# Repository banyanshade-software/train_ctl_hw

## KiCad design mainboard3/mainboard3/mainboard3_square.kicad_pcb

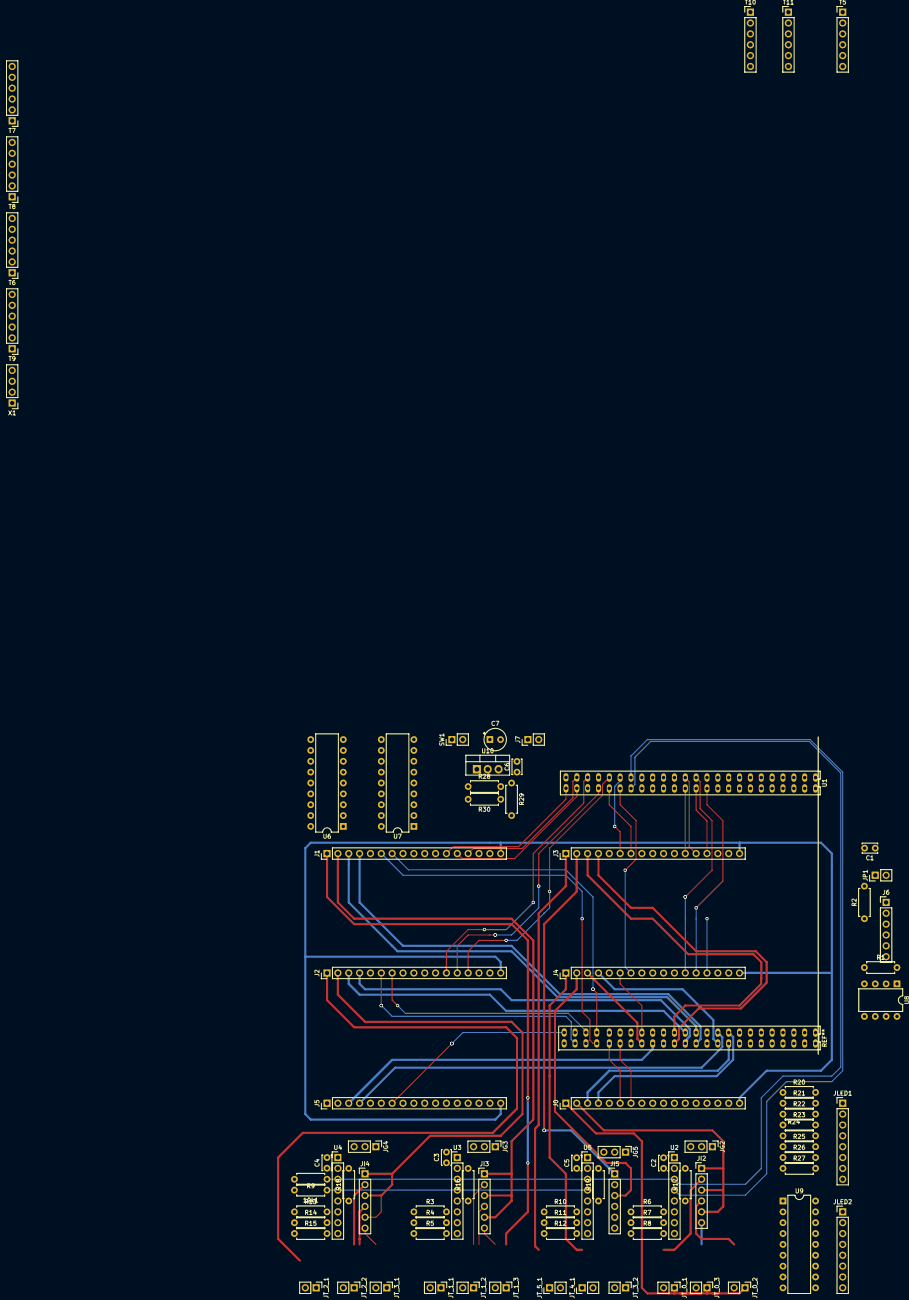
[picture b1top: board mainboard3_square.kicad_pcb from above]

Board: 2 copper layers, 88 parts (0 on the bottom side), 157 nets.

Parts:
10k1: R; R_Axial_DIN0207_L6.3mm_D2.5mm_P7.62mm_Horizontal
C1, C2, C3, C4, C5: 100nF; C_Disc_D3.4mm_W2.1mm_P2.50mm
C6: 0.1µF; C_Disc_D3.4mm_W2.1mm_P2.50mm
C7: 10µF; CP_Radial_Tantal_D5.0mm_P2.50mm
J0, J1, J2, J3, J4, J5: Conn_01x18; PinHeader_1x17_P2.54mm_Vertical
J6: Conn_01x06_Female; PinHeader_1x06_P2.54mm_Vertical
J7: Conn_01x02_Female; PinHeader_1x02_P2.54mm_Vertical
JG2, JG3, JG4, JG5: Conn_01x03_Female; PinHeader_1x03_P2.54mm_Vertical
JI2, JI3, JI4, JI5: Conn_01x06_Female; PinHeader_1x06_P2.54mm_Vertical
JLED1, JLED2: Conn_01x08_Female; PinHeader_1x08_P2.54mm_Vertical
JP1: Jumper; PinHeader_1x02_P2.54mm_Vertical
JT_0_1, JT_0_2, JT_0_3, JT_1_1, JT_1_2, JT_1_3, JT_2_1, JT_2_2, JT_3_1, JT_3_2, JT_4_1, JT_5_1: Screw_Terminal_01x02; PinHeader_1x02_P2.54mm_Vertical
R1, R20, R21, R22, R23, R24, R25, R26, R27: R; R_Axial_DIN0207_L6.3mm_D2.5mm_P7.62mm_Horizontal
R2: 120; R_Axial_DIN0207_L6.3mm_D2.5mm_P7.62mm_Horizontal
R3, R4, R5, R6, R7, R8, R9, R10, R11, R12, R13, R14, R15, R16, R17, R18, R19: 10k; R_Axial_DIN0207_L6.3mm_D2.5mm_P7.62mm_Horizontal
R28: 510; R_Axial_DIN0207_L6.3mm_D2.5mm_P7.62mm_Horizontal
R29: 200; R_Axial_DIN0207_L6.3mm_D2.5mm_P7.62mm_Horizontal
R30: 240; R_Axial_DIN0207_L6.3mm_D2.5mm_P7.62mm_Horizontal
SW1: SW_DIP_x01; PinHeader_1x02_P2.54mm_Vertical
T5, T6, T7, T8, T9, T10, T11: Screw_Terminal_01x06; PinHeader_1x06_P2.54mm_Vertical
U1: STM32_F4xx; STM32_F4XXrev
U2, U3, U4, U5: ModuleINA3221; PinHeader_1x08_P2.54mm_Vertical
U6, U7, U9: ULN2803A; DIP-18_W7.62mm
U8: MCP2551-I-P; DIP-8_W7.62mm
U10: LM317_TO220; TO-220-3_Vertical
X1: Screw_Terminal_01x04; PinHeader_1x04_P2.54mm_Vertical

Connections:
3V3: C2.2, C3.2, C4.2, C5.2, R3.1, R4.1, R5.1, R6.1, R7.1, R8.1, R10.1, R11.1, R12.1, R13.1, R14.1, R15.1, T10.2, U1.1, U1.2, U1.3, U1.4, U1.53, U1.54, U1.55, U1.56, U2.1, U3.1, U4.1, U5.1
5V: R20.1, R21.1, R22.1, R23.1, R24.1, R25.1, R26.1, R27.1, U1.49, U1.50, U1.51, U1.52, U9.10, X1.3
12Vunreg: C6.1, J0.17, J1.17, J2.17, J3.17, J4.17, J5.17, J7.2, T6.2, T6.5, T7.2, T7.5, T8.2, T8.5, T9.2, T9.5, U6.10, U7.10, U10.3, X1.1
+5V: C1.2, J6.3, U8.3
CAN_RX: U1.13, U8.4
CAN_TX: U1.14, U8.1
CT0_1: J0.12, U1.61
CT0_2: J0.13, U1.59
CT0_3: J0.14, U1.60
CT1_1: J1.12, U1.48
CT1_2: J1.13, U1.46
CT1_3: J1.14, U1.45
CT2_1: J2.12, U1.43
CT2_2: J2.13, U1.42
CT2_3: J2.14, U1.39
CT3_1: J3.12, U1.26
CT3_2: J3.13, U1.25
CT3_3: J3.14, U1.24
CT4_1: J4.12, U1.23
CT4_2: J4.13, U1.22
CT4_3: J4.14, U1.21
CT5_1: J5.12, U1.83
CT5_2: J5.13, U1.85
CT5_3: J5.14, U1.87
ETR1: T5.5, U1.84
GND: 10k1.2, C1.1, C2.1, C3.1, C4.1, C5.1, C6.2, C7.2, J0.16, J1.16, J2.16, J3.16, J4.16, J5.16, J6.2, J7.1, JG2.1, JG2.2, JG3.1, JG3.2, JG4.1, JG4.2, JG5.1, JG5.2, R1.1, R9.2, R29.2, T5.1, T10.1, U1.7, U1.8, U1.9, U1.10, U1.57, U1.58, U2.2, U3.2, U4.2, U5.2, U6.9, U7.9, U8.2, U9.9, X1.2
I1A: J0.2, JI2.1, JI2.3, JI2.5
I1B: JI2.2, JT_0_1.2
I2B: JI2.4, JT_0_2.2
I2C1_SCL: T5.4, T10.4, U1.15
I2C1_SDA: T5.3, T10.3, U1.16
I2C3_SCL: R9.1, U1.36, U2.3, U3.3, U4.3, U5.3
I2C3_SDA: 10k1.1, U1.35, U2.4, U3.4, U4.4, U5.4
I3B: JI2.6, JT_0_3.2
I4A: J1.2, JI3.1, JI3.3, JI3.5
I4B: JI3.2, JT_1_1.2
I5B: JI3.4, JT_1_2.2
I6B: JI3.6, JT_1_3.2
I7A: J2.2, JI4.1, JI4.3, JI4.5
I7B: JI4.2, JT_2_1.2
I8B: JI4.4, JT_2_2.2
I9B: JI4.6, JT_3_1.2
I10A: J3.2, JI5.1
I10B: JI5.2, JT_3_2.2
I11A: J4.2, JI5.3
I11B: JI5.4, JT_4_1.2
I12A: J5.2, JI5.5
I12B: JI5.6, JT_5_1.2
unnamed: C7.1, R30.1, SW1.1, U10.2
unnamed: J6.5, R2.1, U8.7
unnamed: J6.6, JP1.1, U8.6
unnamed: JG2.3, R17.2
unnamed: JG3.3, R16.2
unnamed: JG4.3, R18.2
unnamed: JG5.3, R19.2
unnamed: JLED1.1, R20.2
unnamed: JLED1.2, U9.18
unnamed: JLED1.3, R21.2
unnamed: JLED1.4, U9.17
unnamed: JLED1.5, R22.2
unnamed: JLED1.6, U9.16
unnamed: JLED1.7, R23.2
unnamed: JLED1.8, U9.15
unnamed: JLED2.1, R24.2
unnamed: JLED2.2, U9.14
unnamed: JLED2.3, R25.2
unnamed: JLED2.4, U9.13
unnamed: JLED2.5, R26.2
unnamed: JLED2.6, U9.12
unnamed: JLED2.7, R27.2
unnamed: JLED2.8, U9.11
unnamed: JP1.2, R2.2
unnamed: R1.2, U8.8
unnamed: R3.2, U3.6
unnamed: R4.2, U3.7
unnamed: R5.2, U3.8
unnamed: R6.2, U2.6
unnamed: R7.2, U2.7
unnamed: R8.2, U2.8
unnamed: R10.2, U5.6
unnamed: R11.2, U5.7
unnamed: R12.2, U5.8
unnamed: R13.2, U4.6
unnamed: R14.2, U4.7
unnamed: R15.2, U4.8
unnamed: R16.1, U3.5
unnamed: R17.1, U2.5
unnamed: R18.1, U4.5
unnamed: R19.1, U5.5
unnamed: R28.1, R30.2, U10.1
unnamed: R28.2, R29.1
unnamed: T6.1, U6.18
unnamed: T6.3, U6.17
unnamed: T6.4, U6.16
unnamed: T6.6, U6.15
unnamed: T7.1, U6.14
unnamed: T7.3, U6.13
unnamed: T7.4, U6.12
unnamed: T7.6, U6.11
unnamed: T8.1, U7.18
unnamed: T8.3, U7.17
unnamed: T8.4, U7.16
unnamed: T8.6, U7.15
unnamed: T9.1, U7.14
unnamed: T9.3, U7.13
unnamed: T9.4, U7.12
unnamed: T9.6, U7.11
PWM0_1: J0.6, U1.88
PWM0_2: J0.7, U1.86
PWM1_1: J1.6, U1.90
PWM1_2: J1.7, U1.89
PWM2_1: J2.6, U1.94
PWM2_2: J2.7, U1.91
PWM3_1: J3.6, U1.37
PWM3_2: J3.7, U1.40
PWM4_1: J4.6, U1.81
PWM4_2: J4.7, U1.38
PWM5_1: J5.6, U1.47
PWM5_2: J5.7, U1.95
R1: T11.2, U1.33
R2: T11.3, U1.34
R5: T11.6, U1.29
ROT1: T10.6, U1.44
ROT2: T10.5, U1.41
TRACK0_0: J0.1, JT_0_1.1, JT_0_2.1, JT_0_3.1
TRACK1_0: J1.1, JT_1_1.1, JT_1_2.1, JT_1_3.1
TRACK2_0: J2.1, JT_2_1.1, JT_2_2.1, JT_3_1.1
TRACK3_0: J3.1, JT_3_2.1
TRACK4_0: J4.1, JT_4_1.1
TRACK5_0: J5.1, JT_5_1.1
TURN1A: U1.93, U6.1
TURN2A: U1.96, U6.3
TURN2B: U1.18, U6.4
TURN3A: U1.19, U6.5
TURN3B: U1.20, U6.6
TURN4A: U1.62, U6.7
TURN4B: U1.64, U6.8
TURN5A: U1.63, U7.1
TURN5B: U1.28, U7.2
TURN6A: U1.79, U7.3
TURN6B: U1.92, U7.4
TURN7A: U1.27, U7.5
TURN7B: U1.30, U7.6
TURN8A: U1.11, U7.7
TURN8B: U1.12, U7.8
VSENSE0_0: J0.3, U1.66
VSENSE0_1: J0.4, U1.65
VSENSE1_0: J1.3, U1.71
VSENSE1_1: J1.4, U1.72
VSENSE2_0: J2.3, U1.73
VSENSE2_1: J2.4, U1.74
VSENSE3_0: J3.3, U1.75
VSENSE3_1: J3.4, U1.76
VSENSE4_0: J4.3, U1.82
VSENSE4_1: J4.4, U1.68
VSENSE5_0: J5.3, U1.80
VSENSE5_1: J5.4, U1.67

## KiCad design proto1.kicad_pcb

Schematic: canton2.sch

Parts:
C1: 0.1µF; C_Disc_D3.4mm_W2.1mm_P2.50mm
C2: 10µF; CP_Radial_Tantal_D5.0mm_P2.50mm
J1: Conn_01x18; PinHeader_1x16_P2.54mm_Horizontal
Q1, Q2, Q3, Q4: PN2222A; TO-92_Inline
R1: 240; R_Axial_DIN0207_L6.3mm_D2.5mm_P10.16mm_Horizontal
R2, R3, R4, R5, R6: R; R_Axial_DIN0207_L6.3mm_D2.5mm_P7.62mm_Horizontal
R7, R8, R9, R10, R15: 2200; R_Axial_DIN0207_L6.3mm_D2.5mm_P7.62mm_Horizontal
R12, R13: 10k; R_Axial_DIN0207_L6.3mm_D2.5mm_P7.62mm_Horizontal
R14: 2200; R_Axial_DIN0207_L6.3mm_D2.5mm_P10.16mm_Horizontal
R16: 3k; R_Axial_DIN0207_L6.3mm_D2.5mm_P7.62mm_Horizontal
U1: LM317_TO220; TO-220-3_Vertical
U2: CJMCU-4080; module_1x8
U3: ModuleDRV8833; module_2x6

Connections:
3.3V: J1.7, U2.4
12Vunreg: C1.1, U1.3 (VI)
CT0: J1.11, R7.2
CT1: J1.12, R8.2
CT2: J1.13, R9.2
CT3: J1.14, R10.2
GND: C1.2, C2.2, J1.16, Q1.1, Q2.1, Q3.1, Q4.1, R2.2, R14.2, R15.2, U2.1, U2.5, U3.10
ISENSE: J1.6, U2.8
unnamed: C2.1, R1.1, U1.2 (VO), U2.3
unnamed: Q1.2, R7.1
unnamed: Q1.3, R3.2
unnamed: Q2.2, R8.1
unnamed: Q2.3, R4.2
unnamed: Q3.2, R9.1
unnamed: Q3.3, R5.2
unnamed: Q4.2, R10.1
unnamed: Q4.3, R6.2
unnamed: R1.2, R2.1, R3.1, R4.1, R5.1, R6.1, U1.1 (ADJ)
unnamed: U2.2, U3.9
PWM1: J1.8, U3.7
PWM2: J1.9, U3.8
TRACK0: J1.1, R13.1, R16.1, U3.2
TRACK1: J1.2, R12.1, R16.2, U3.3
VSENSE0: J1.5, R12.2, R14.1
VSENSE1: J1.4, R13.2, R15.1

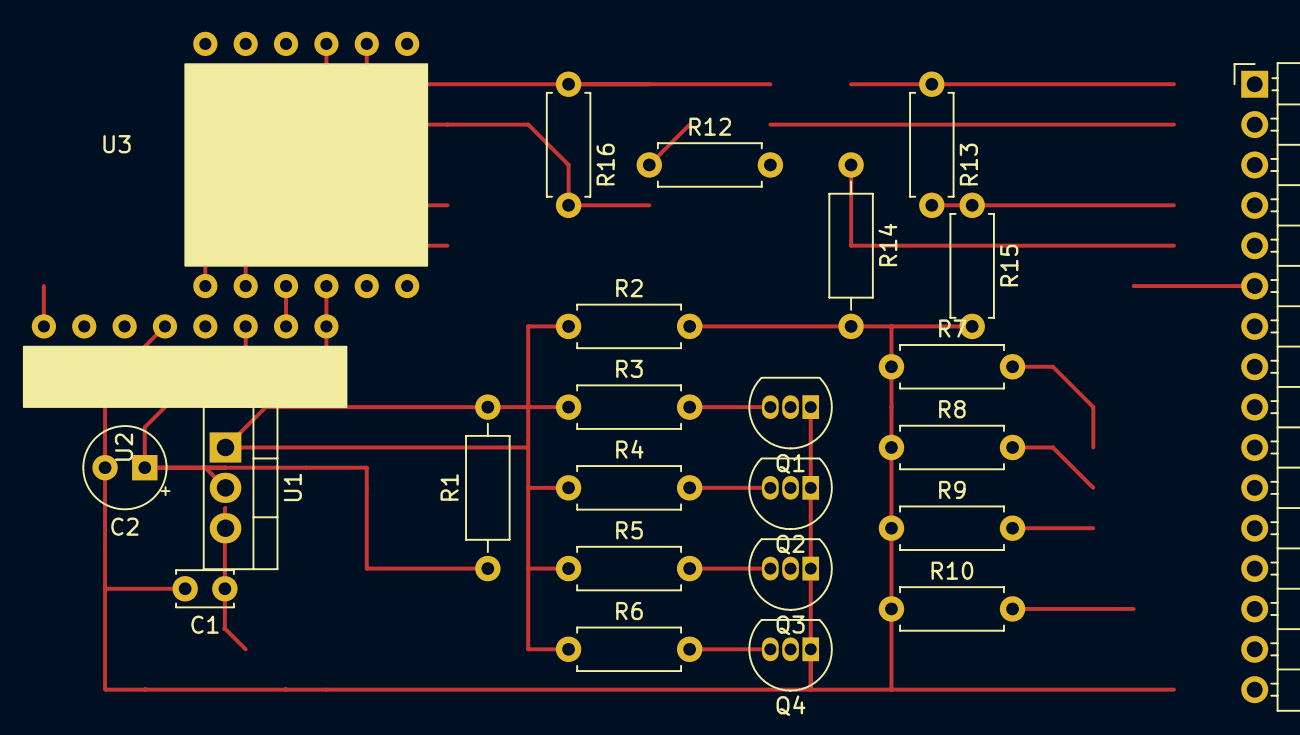
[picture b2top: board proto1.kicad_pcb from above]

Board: 2 copper layers, 25 parts (0 on the bottom side), 25 nets.

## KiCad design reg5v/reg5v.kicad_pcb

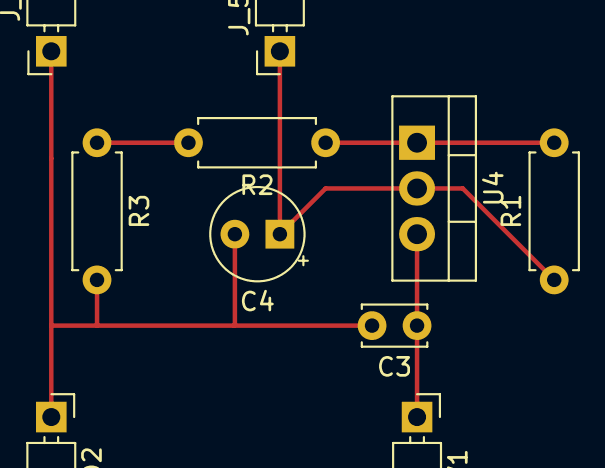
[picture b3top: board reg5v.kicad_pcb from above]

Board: 2 copper layers, 10 parts (0 on the bottom side), 5 nets.

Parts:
C3: 0.1µF; C_Disc_D3.4mm_W2.1mm_P2.50mm
C4: 10µF; CP_Radial_Tantal_D5.0mm_P2.50mm
J_5VOUT1, J_12V1: Conn_01x01; PinHeader_1x01_P2.54mm_Horizontal
J_GND1, J_GND2: Conn_01x01; PinHeader_1x01_P2.54mm_Horizontal
R1: 240; R_Axial_DIN0207_L6.3mm_D2.5mm_P7.62mm_Horizontal
R2: 510; R_Axial_DIN0207_L6.3mm_D2.5mm_P7.62mm_Horizontal
R3: 200; R_Axial_DIN0207_L6.3mm_D2.5mm_P7.62mm_Horizontal
U4: LM317_TO220; TO-220-3_Vertical

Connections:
12Vunreg: C3.1, J_12V1.1, U4.3
GND: C3.2, C4.2, J_GND1.1, J_GND2.1, R3.2
unnamed: R1.2, R2.1, U4.1
unnamed: R2.2, R3.1
V5: C4.1, J_5VOUT1.1, R1.1, U4.2
